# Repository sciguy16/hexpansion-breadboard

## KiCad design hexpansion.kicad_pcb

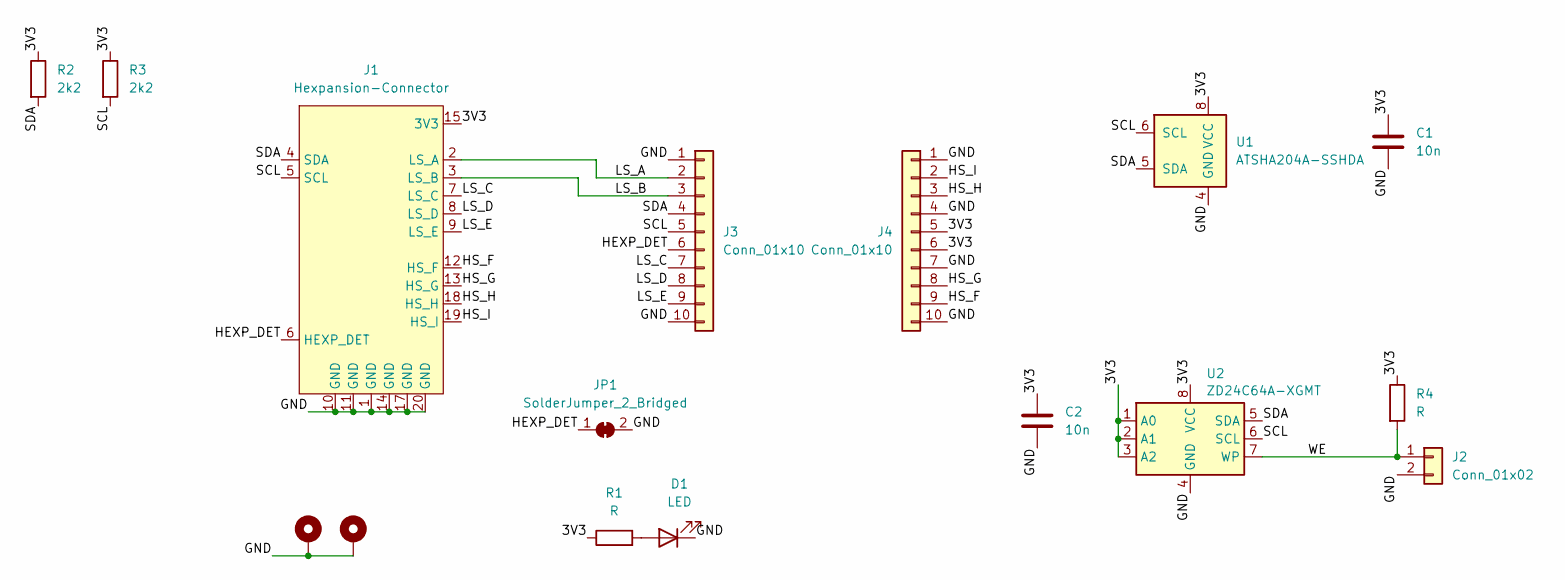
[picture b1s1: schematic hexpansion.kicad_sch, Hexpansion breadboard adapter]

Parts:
C1, C2: 10n; C_0603_1608Metric
D1: LED; LED_0603_1608Metric
H1, H2: MountingHole_Pad; MountingHole_2.2mm_M2_Pad_Via
J1: Hexpansion-Connector; hexpansion-edge-connector
J2: Conn_01x02; PinHeader_1x02_P2.54mm_Vertical
J3, J4: Conn_01x10; PinHeader_1x10_P2.54mm_Vertical
JP1: SolderJumper_2_Bridged; SolderJumper-2_P1.3mm_Bridged_RoundedPad1.0x1.5mm
R1, R4: R; R_0603_1608Metric
R2, R3: 2k2; R_0603_1608Metric
U1: ATSHA204A-SSHDA; SOIC-8_3.9x4.9mm_P1.27mm
U2: ZD24C64A-XGMT; TSSOP-8_4.4x3mm_P0.65mm

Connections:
/3V3: C1.1, C2.1, J1.15 (3V3), J1.16 (3V3), J4.5, J4.6, R1.1, R2.1, R3.1, R4.1, U1.8 (VCC), U2.1 (A0), U2.2 (A1), U2.3 (A2), U2.8 (VCC)
/GND: C1.2, C2.2, D1.1 (K), H1.1, H2.1, J1.1 (GND), J1.10 (GND), J1.11 (GND), J1.14 (GND), J1.17 (GND), J1.20 (GND), J2.2, J3.1, J3.10, J4.1, J4.4, J4.7, J4.10, JP1.2 (B), U1.4 (GND), U2.4 (GND)
/HEXP_DET: J1.6 (HEXP_DET), J3.6, JP1.1 (A)
/HS_F: J1.12 (HS_F), J4.9
/HS_G: J1.13 (HS_G), J4.8
/HS_H: J1.18 (HS_H), J4.3
/HS_I: J1.19 (HS_I), J4.2
/LS_A: J1.2 (LS_A), J3.2
/LS_B: J1.3 (LS_B), J3.3
/LS_C: J1.7 (LS_C), J3.7
/LS_D: J1.8 (LS_D), J3.8
/LS_E: J1.9 (LS_E), J3.9
/SCL: J1.5 (SCL), J3.5, R3.2, U1.6 (SCL), U2.6 (SCL)
/SDA: J1.4 (SDA), J3.4, R2.2, U1.5 (SDA), U2.5 (SDA)
/WE: J2.1, R4.2, U2.7 (WP)
unnamed: D1.2 (A), R1.2

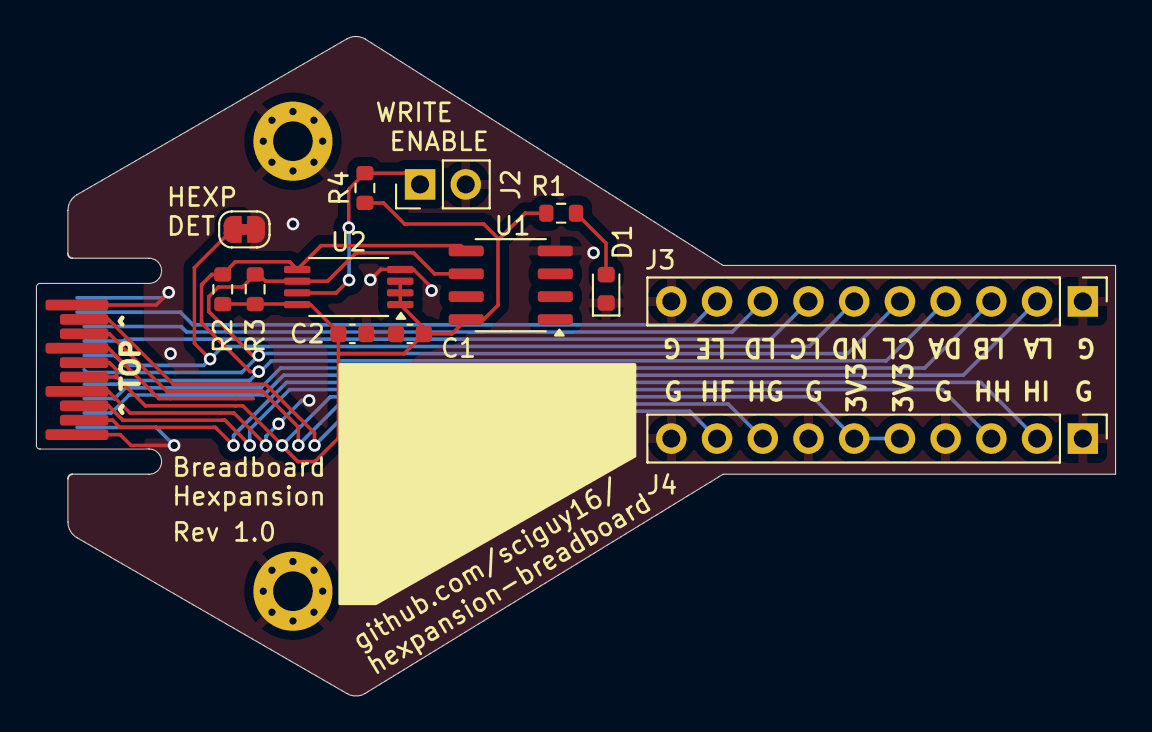
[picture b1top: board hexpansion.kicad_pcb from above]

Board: 2 copper layers, 59.9 x 36.6 mm, 16 parts (0 on the bottom side), 16 nets.

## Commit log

2024-06-08 Bring over example project
2024-06-09 Initial revision
